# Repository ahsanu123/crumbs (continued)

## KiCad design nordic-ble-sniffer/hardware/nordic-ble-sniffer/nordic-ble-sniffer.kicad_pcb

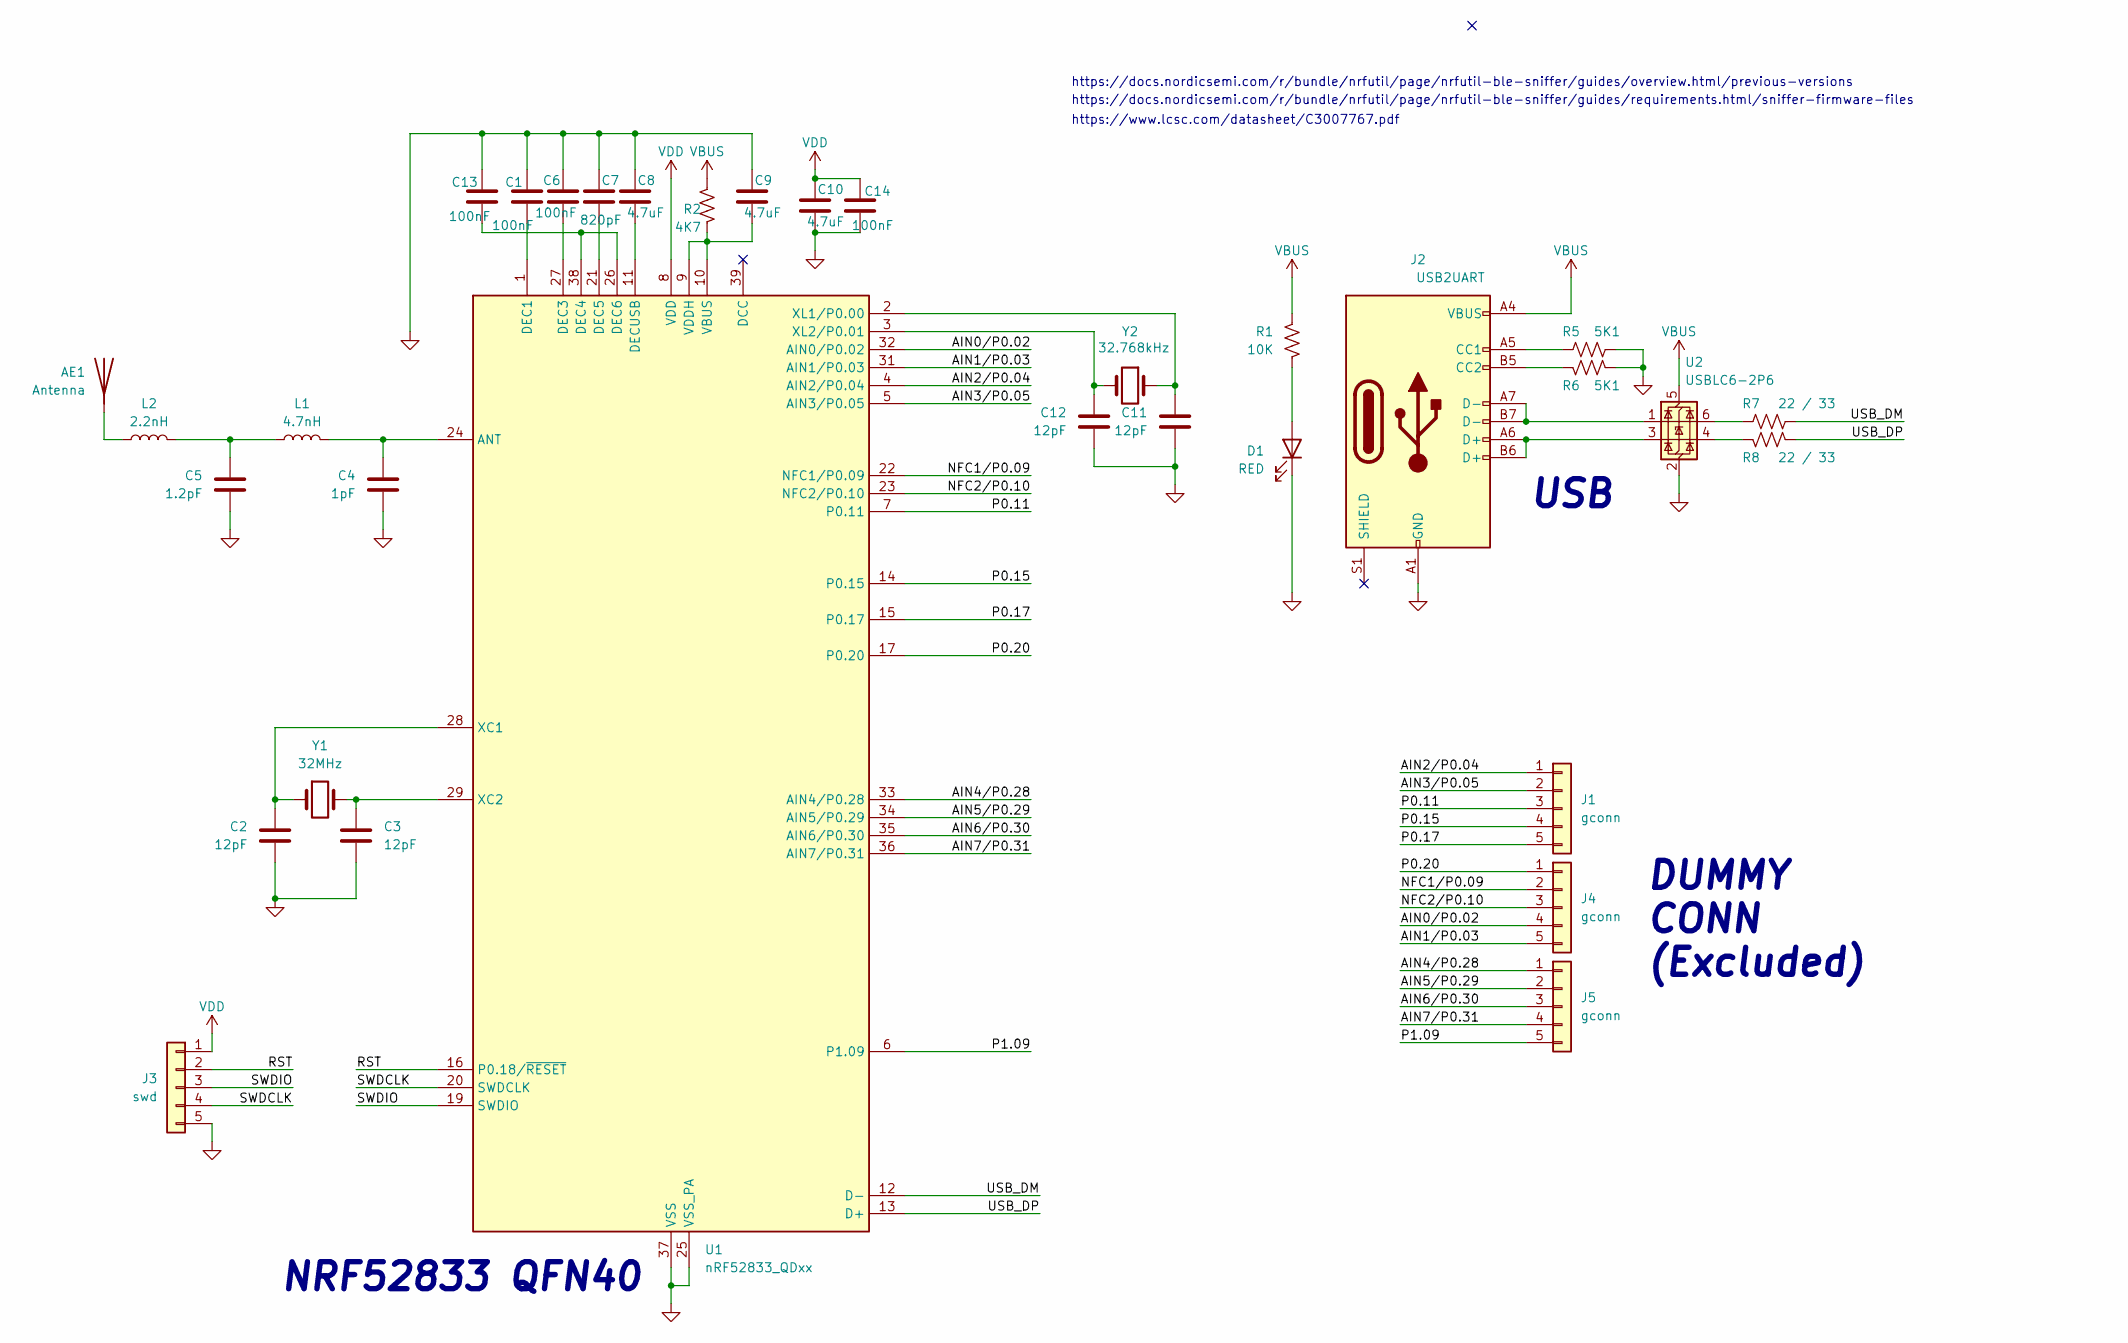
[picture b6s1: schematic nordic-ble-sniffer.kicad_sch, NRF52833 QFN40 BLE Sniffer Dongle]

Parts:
AE1: Antenna; Texas_SWRA117D_2.4GHz_Left
C1, C6, C13, C14: 100nF; C_0805_2012Metric_Pad1.18x1.45mm_HandSolder
C2, C3, C11, C12: 12pF; C_0805_2012Metric_Pad1.18x1.45mm_HandSolder
C4: 1pF; C_0805_2012Metric_Pad1.18x1.45mm_HandSolder
C5: 1.2pF; C_0805_2012Metric_Pad1.18x1.45mm_HandSolder
C7: 820pF; C_0805_2012Metric_Pad1.18x1.45mm_HandSolder
C8, C9, C10: 4.7uF; C_0805_2012Metric_Pad1.18x1.45mm_HandSolder
D1: RED; LED_1206_3216Metric_Pad1.42x1.75mm_HandSolder
J1, J4, J5: gconn; PinHeader_1x05_P2.54mm_Vertical
J2: USB2UART; USB_C_Receptacle_GCT_USB4110
J3: swd; PinHeader_1x05_P2.54mm_Vertical
L1: 4.7nH; L_0805_2012Metric_Pad1.05x1.20mm_HandSolder
L2: 2.2nH; L_0805_2012Metric_Pad1.05x1.20mm_HandSolder
R1: 10K; R_0805_2012Metric_Pad1.20x1.40mm_HandSolder
R2: 4K7; R_0805_2012Metric_Pad1.20x1.40mm_HandSolder
R5, R6: 5K1; R_0805_2012Metric_Pad1.20x1.40mm_HandSolder
R7, R8: 22 / 33; R_0805_2012Metric_Pad1.20x1.40mm_HandSolder
U1: nRF52833_QDxx; QFN-40-1EP_5x5mm_P0.4mm_EP3.6x3.6mm
U2: USBLC6-2P6; SOT-666
Y1: 32MHz; Crystal_HC49-U_Vertical
Y2: 32.768kHz; Crystal_HC49-U_Vertical

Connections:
/AIN0/P0.02: J4.4, U1.32 (AIN0/P0.02)
/AIN1/P0.03: J4.5, U1.31 (AIN1/P0.03)
/AIN2/P0.04: J1.1, U1.4 (AIN2/P0.04)
/AIN3/P0.05: J1.2, U1.5 (AIN3/P0.05)
/AIN4/P0.28: J5.1, U1.33 (AIN4/P0.28)
/AIN5/P0.29: J5.2, U1.34 (AIN5/P0.29)
/AIN6/P0.30: J5.3, U1.35 (AIN6/P0.30)
/AIN7/P0.31: J5.4, U1.36 (AIN7/P0.31)
/NFC1/P0.09: J4.2, U1.22 (NFC1/P0.09)
/NFC2/P0.10: J4.3, U1.23 (NFC2/P0.10)
/P0.11: J1.3, U1.7 (P0.11)
/P0.15: J1.4, U1.14 (P0.15)
/P0.17: J1.5, U1.15 (P0.17)
/P0.20: J4.1, U1.17 (P0.20)
/P1.09: J5.5, U1.6 (P1.09)
/RST: J3.2, U1.16 (P0.18/~RESET)
/SWDCLK: J3.4, U1.20 (SWDCLK)
/SWDIO: J3.3, U1.19 (SWDIO)
/USB_DM: R7.1, U1.12 (D-)
/USB_DP: R8.1, U1.13 (D+)
GND: C1.2, C2.2, C3.2, C4.2, C5.2, C6.1, C7.1, C8.1, C9.1, C10.2, C11.2, C12.2, C13.2, C14.1, D1.1 (K), J2.A1 (GND), J2.A12 (GND), J2.B1 (GND), J2.B12 (GND), J3.5, R5.1, R6.1, U1.25 (VSS_PA), U1.37 (VSS), U1.41 (VSS), U2.2 (GND)
unnamed: AE1.1 (A_1), L2.1
unnamed: C5.1, L1.1, L2.2
unnamed: D1.2 (A), R1.2
unnamed: J2.A5 (CC1), R5.2
unnamed: J2.B5 (CC2), R6.2
unnamed: J2.A6 (D+), J2.B6 (D+), U2.3 (I/O2)
unnamed: J2.A7 (D-), J2.B7 (D-), U2.1 (I/O1)
unnamed: R7.2, U2.6 (I/O1)
unnamed: R8.2, U2.4 (I/O2)
unnamed: C4.1, L1.2, U1.24 (ANT)
unnamed: C1.1, U1.1 (DEC1)
unnamed: C6.2, U1.27 (DEC3)
unnamed: C13.1, U1.26 (DEC6), U1.38 (DEC4)
unnamed: C7.2, U1.21 (DEC5)
unnamed: C8.2, U1.11 (DECUSB)
unnamed: C9.2, R2.2, U1.9 (VDDH), U1.10 (VBUS)
unnamed: C2.1, U1.28 (XC1), Y1.1
unnamed: C3.1, U1.29 (XC2), Y1.2
unnamed: C11.1, U1.2 (XL1/P0.00), Y2.1
unnamed: C12.1, U1.3 (XL2/P0.01), Y2.2
VBUS: J2.A4 (VBUS), J2.A9 (VBUS), J2.B4 (VBUS), J2.B9 (VBUS), R1.1, R2.1, U2.5 (VBUS)
VDD: C10.1, C14.2, J3.1, U1.8 (VDD), U1.18 (VDD), U1.30 (VDD), U1.40 (VDD)

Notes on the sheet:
DUMMY CONN (Excluded)
https://docs.nordicsemi.com/r/bundle/nrfutil/page/nrfutil-ble-sniffer/guides/overview.html/previous-versions
https://docs.nordicsemi.com/r/bundle/nrfutil/page/nrfutil-ble-sniffer/guides/requirements.html/sniffer-firmware-files
USB
https://www.lcsc.com/datasheet/C3007767.pdf
NRF52833 QFN40

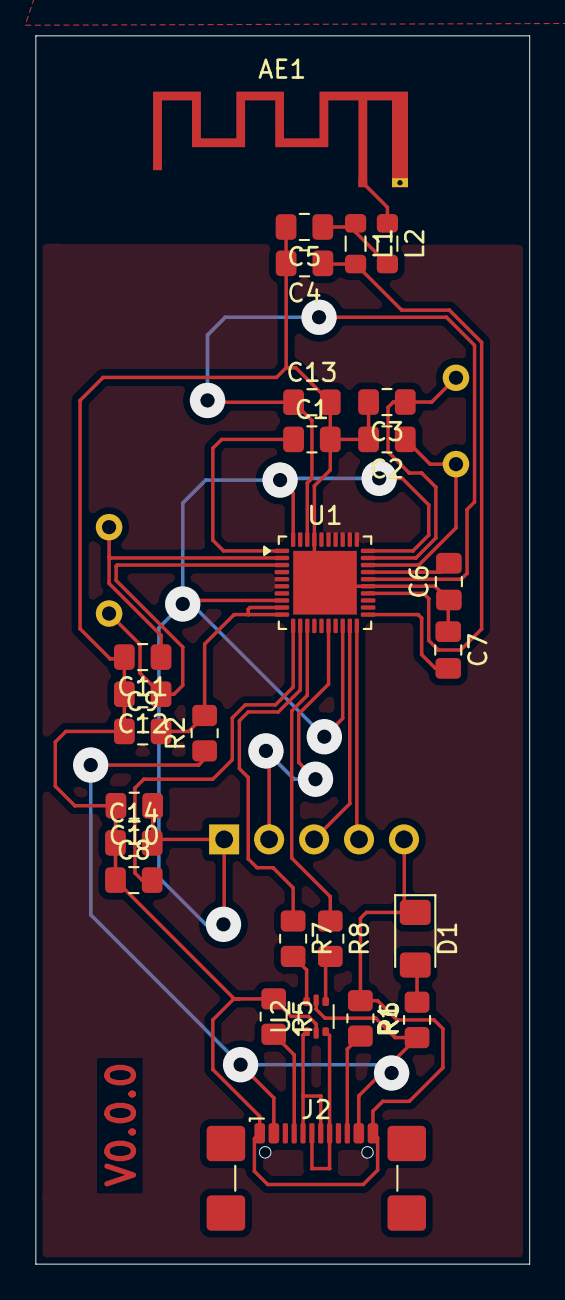
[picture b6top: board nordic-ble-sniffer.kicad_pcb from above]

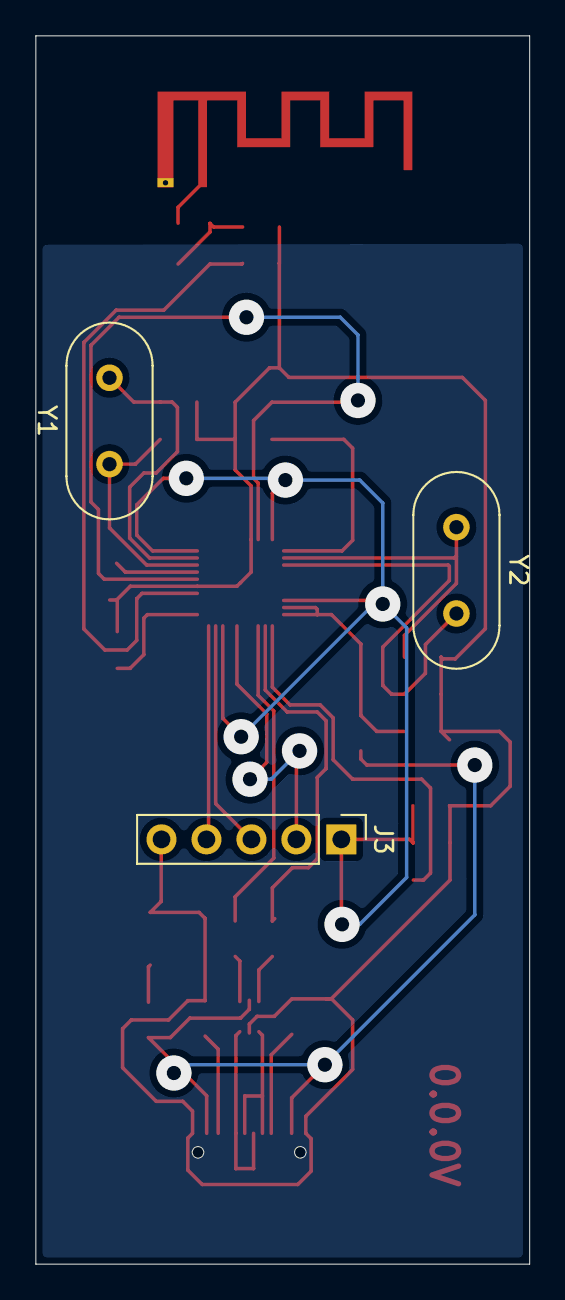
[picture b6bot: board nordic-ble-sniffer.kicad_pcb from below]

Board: 2 copper layers, 27.9 x 69.4 mm, 30 parts (3 on the bottom side), 28 nets.
